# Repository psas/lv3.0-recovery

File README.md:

# lv3_recovery
Recovery system design and analysis.

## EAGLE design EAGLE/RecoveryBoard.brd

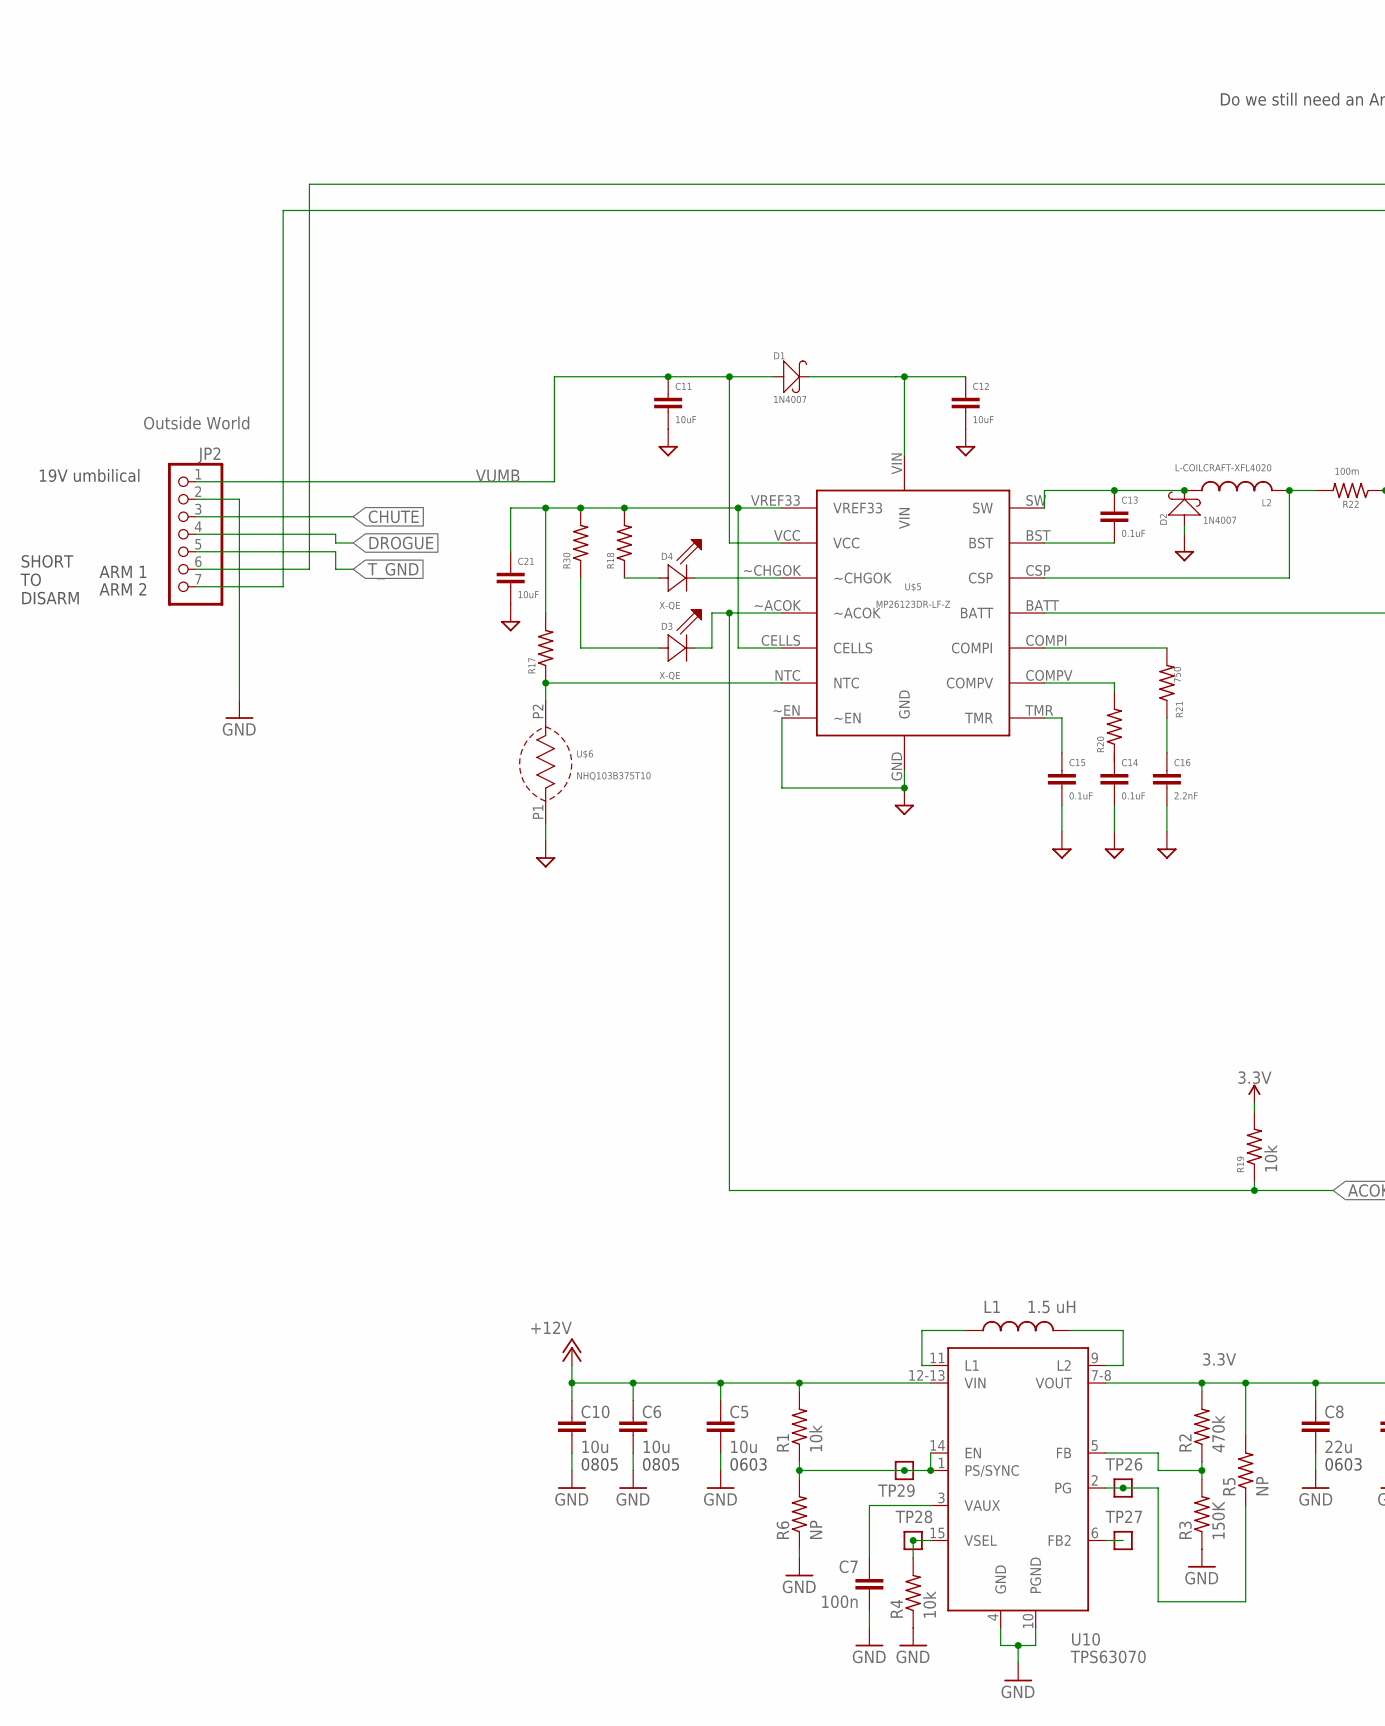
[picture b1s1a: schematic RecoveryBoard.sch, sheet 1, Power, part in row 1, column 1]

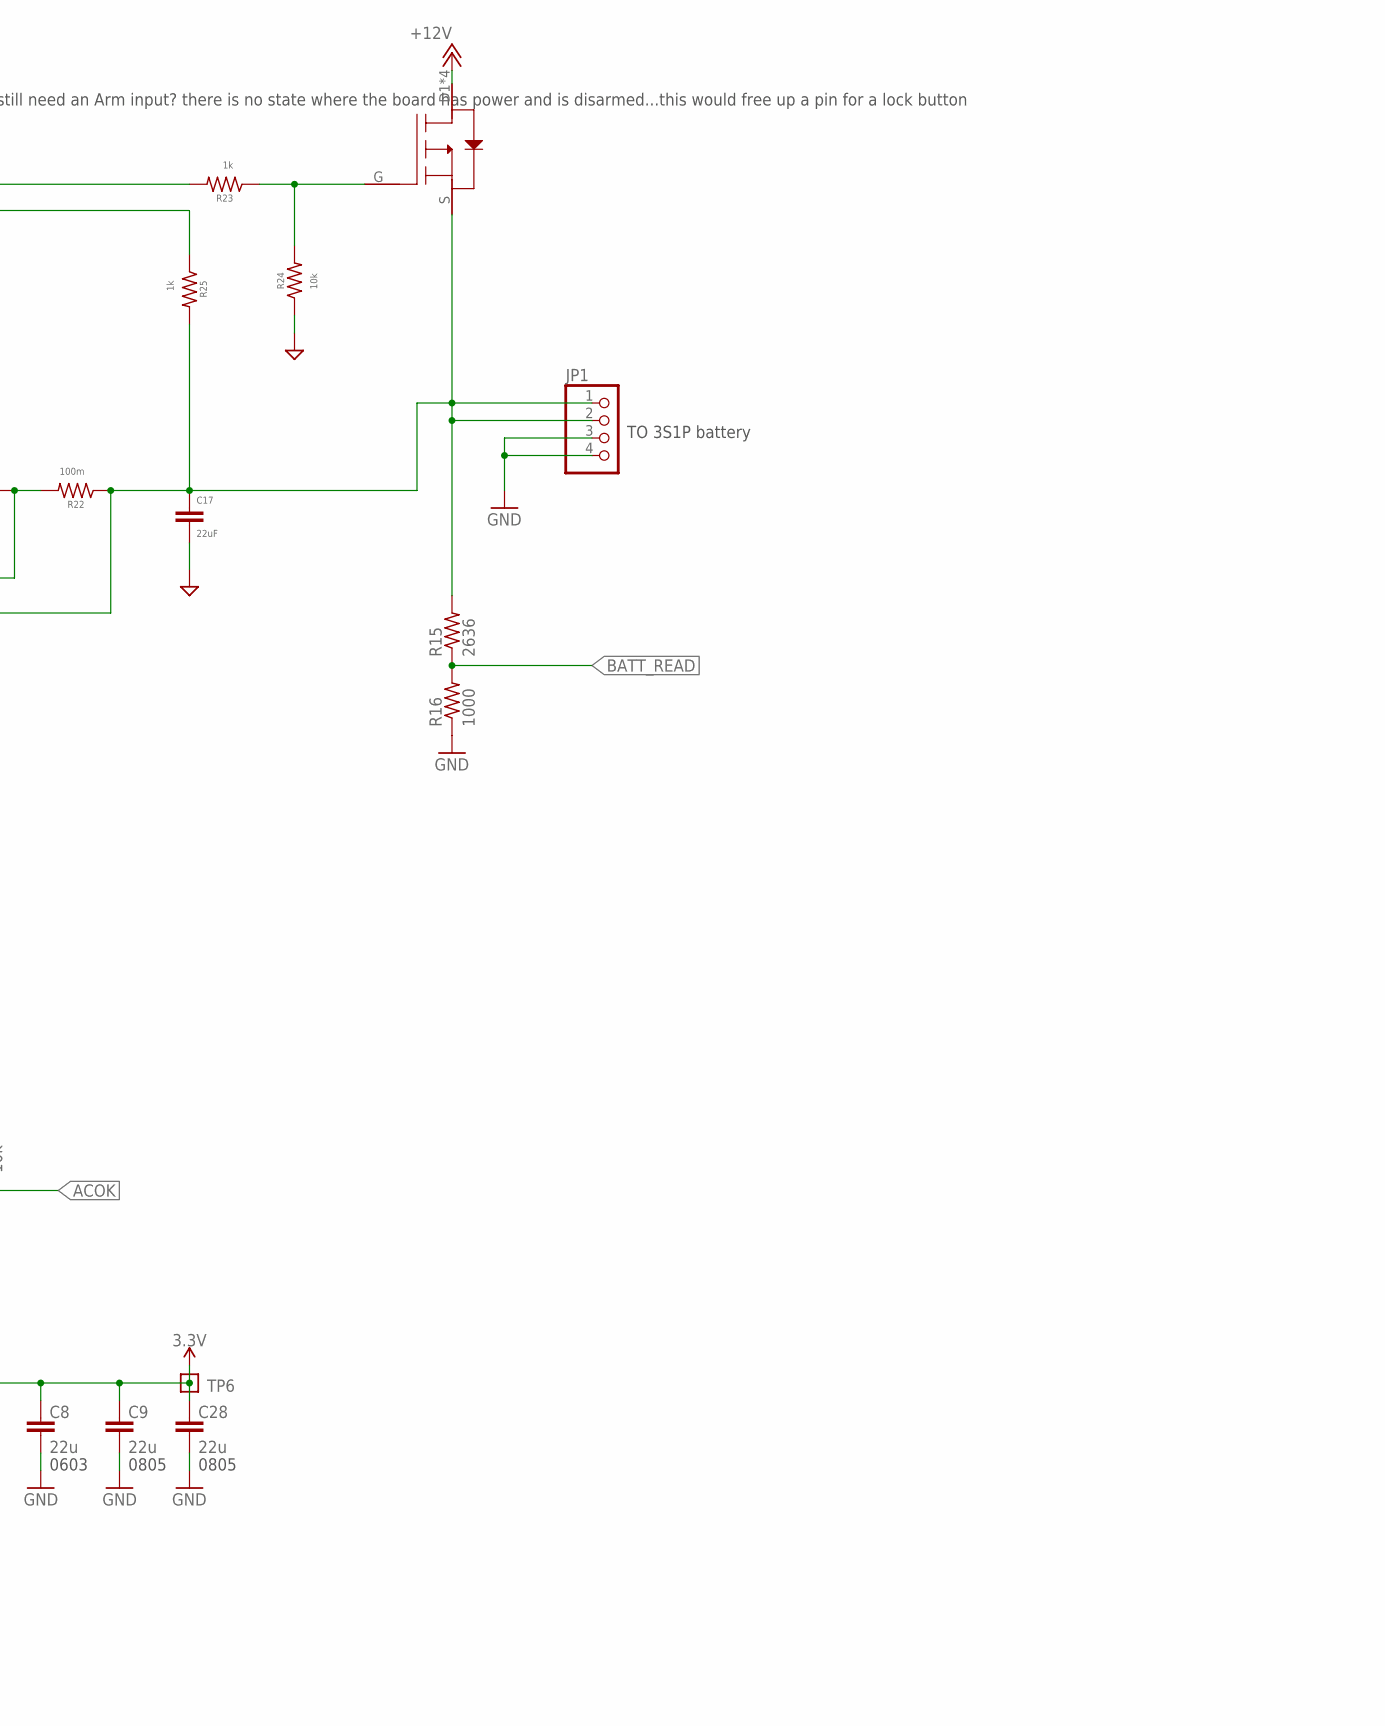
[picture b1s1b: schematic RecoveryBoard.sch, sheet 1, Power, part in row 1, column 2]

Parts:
C5: 10u; .0603-B-NOSILK; MPN CL05B104KO5NNNC
C6, C10: 10u; .0805-B-NOSILK
C7: 100n; .0402-B-NOSILK; MPN CL05B104KO5NNNC
C8: 22u; .0603-B-NOSILK; MPN CL05B104KO5NNNC
C9, C28: 22u; .0805-B-NOSILK
C11, C12, C21: 10uF; .0805-C-NOSILK
C13, C14, C15: 0.1uF; .0603-C-NOSILK
C16: 2.2nF; .0603-C-NOSILK
C17: 22uF; .0603-C-NOSILK
D1, D2: 1N4007; DO-214AC
D3, D4: X-QE
JP1: PINHD-1X4; 1X04
JP2: PINHD-1X7; 1X07
L1: 1.5 uH; L-COILCRAFT-XFL4020; MPN XFL4020-152ME
L2: L-COILCRAFT-XFL4020
R1, R4: 10k; .0402-B-NOSILK; MPN RC1005F6653CS
R2: 470k; .0402-B-NOSILK; MPN RC1005F6653CS
R3: 150K; .0402-B-NOSILK; MPN RC1005F6653CS
R5, R6: NP; .0402-B-NOSILK; MPN RC1005F6653CS
R15: 2636; .0603-C-NOSILK; MPN RC1005F6653CS
R16: 1000; .0603-C-NOSILK; MPN RC1005F6653CS
R17, R18, R20, R30: R-US_0603-C-NOSILK; .0603-C-NOSILK
R19, R24: 10k; .0603-C-NOSILK
R21: 750; .0603-C-NOSILK
R22: 100m; 1206-C
R23, R25: 1k; .0603-C-NOSILK
TP6, TP26, TP27, TP28, TP29: TEST-POINT; 2MM-TEST-POINT
U10: TPS63070; TPS63070X
U$5: MP26123DR-LF-Z
U$6: NHQ103B375T10
U$8: AO6405

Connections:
3.3V: C8.1, C9.1, C28.1, R2.2, R5.2, R19.2, TP6.1, U10.7-8 (VOUT); also elsewhere on the board
+12V: C5.1, C6.1, C10.1, R1.2, U10.12-13 (VIN), U$8.D1 (D), U$8.D2 (D), U$8.D3 (D), U$8.D4 (D); also elsewhere on the board
ACOK: D3.CATHODE (C), R19.1, U$5.~ACOK; also elsewhere on the board
BATT_READ: R15.1, R16.2; also elsewhere on the board
CHUTE: JP2.3; also elsewhere on the board
DROGUE: JP2.4; also elsewhere on the board
GND: C5.2, C6.2, C7.2, C8.2, C9.2, C10.2, C11.2, C12.2, C14.2, C15.2, C16.2, C17.2, C21.2, C28.2, D2.1 (+), JP1.3, JP1.4, JP2.2, R3.1, R4.1, R6.1, R16.1, R24.1, U10.4 (GND), U10.10 (PGND), U$5.EP, U$5.GND, U$5.~EN, U$6.P1; also elsewhere on the board
unnamed: C12.1, D1.2 (-), U$5.VIN
unnamed: C13.1, D2.2 (-), L2.1, U$5.SW
unnamed: C13.2, U$5.BST
unnamed: C21.1, R17.2, R18.2, R30.2, U$5.CELLS, U$5.VREF33
unnamed: D4.CATHODE (C), U$5.~CHGOK
unnamed: D3.ANODE (A), R30.1
unnamed: JP2.6, R23.2
unnamed: R23.1, R24.2, U$8.G
unnamed: D4.ANODE (A), R18.1
unnamed: R20.2, U$5.COMPV
unnamed: C15.1, U$5.TMR
unnamed: R17.1, U$5.NTC, U$6.P2
unnamed: R21.2, U$5.COMPI
unnamed: C16.1, R21.1
unnamed: C17.1, JP1.1, JP1.2, R15.2, R22.1, R25.2, U$5.BATT, U$8.S
unnamed: L2.2, R22.2, U$5.CSP
unnamed: C14.1, R20.1
TPS-EN: R1.1, R6.2, TP29.1, U10.1 (PS/SYNC), U10.14 (EN)
TPS-FB: R2.1, R3.2, U10.5 (FB)
TPS-FB2: TP27.1, U10.6 (FB2)
TPS-L1: L1.1, U10.11 (L1)
TPS-L2: L1.2, U10.9 (L2)
TPS-PG: R5.1, TP26.1, U10.2 (PG)
TPS-VAUX: C7.1, U10.3 (VAUX)
TPS-VSEL: R4.2, TP28.1, U10.15 (VSEL)
T_GND: JP2.5; also elsewhere on the board
VBAT: JP2.7, R25.1
VUMB: C11.1, D1.1 (+), JP2.1, U$5.VCC

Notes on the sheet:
0603
0805
Outside World
TO 3S1P battery
ARM 1
ARM 2
SHORT TO DISARM
19V umbilical
Do we still need an Arm input? there is no state where the board has power and is disarmed...this would free up a pin for a lock button

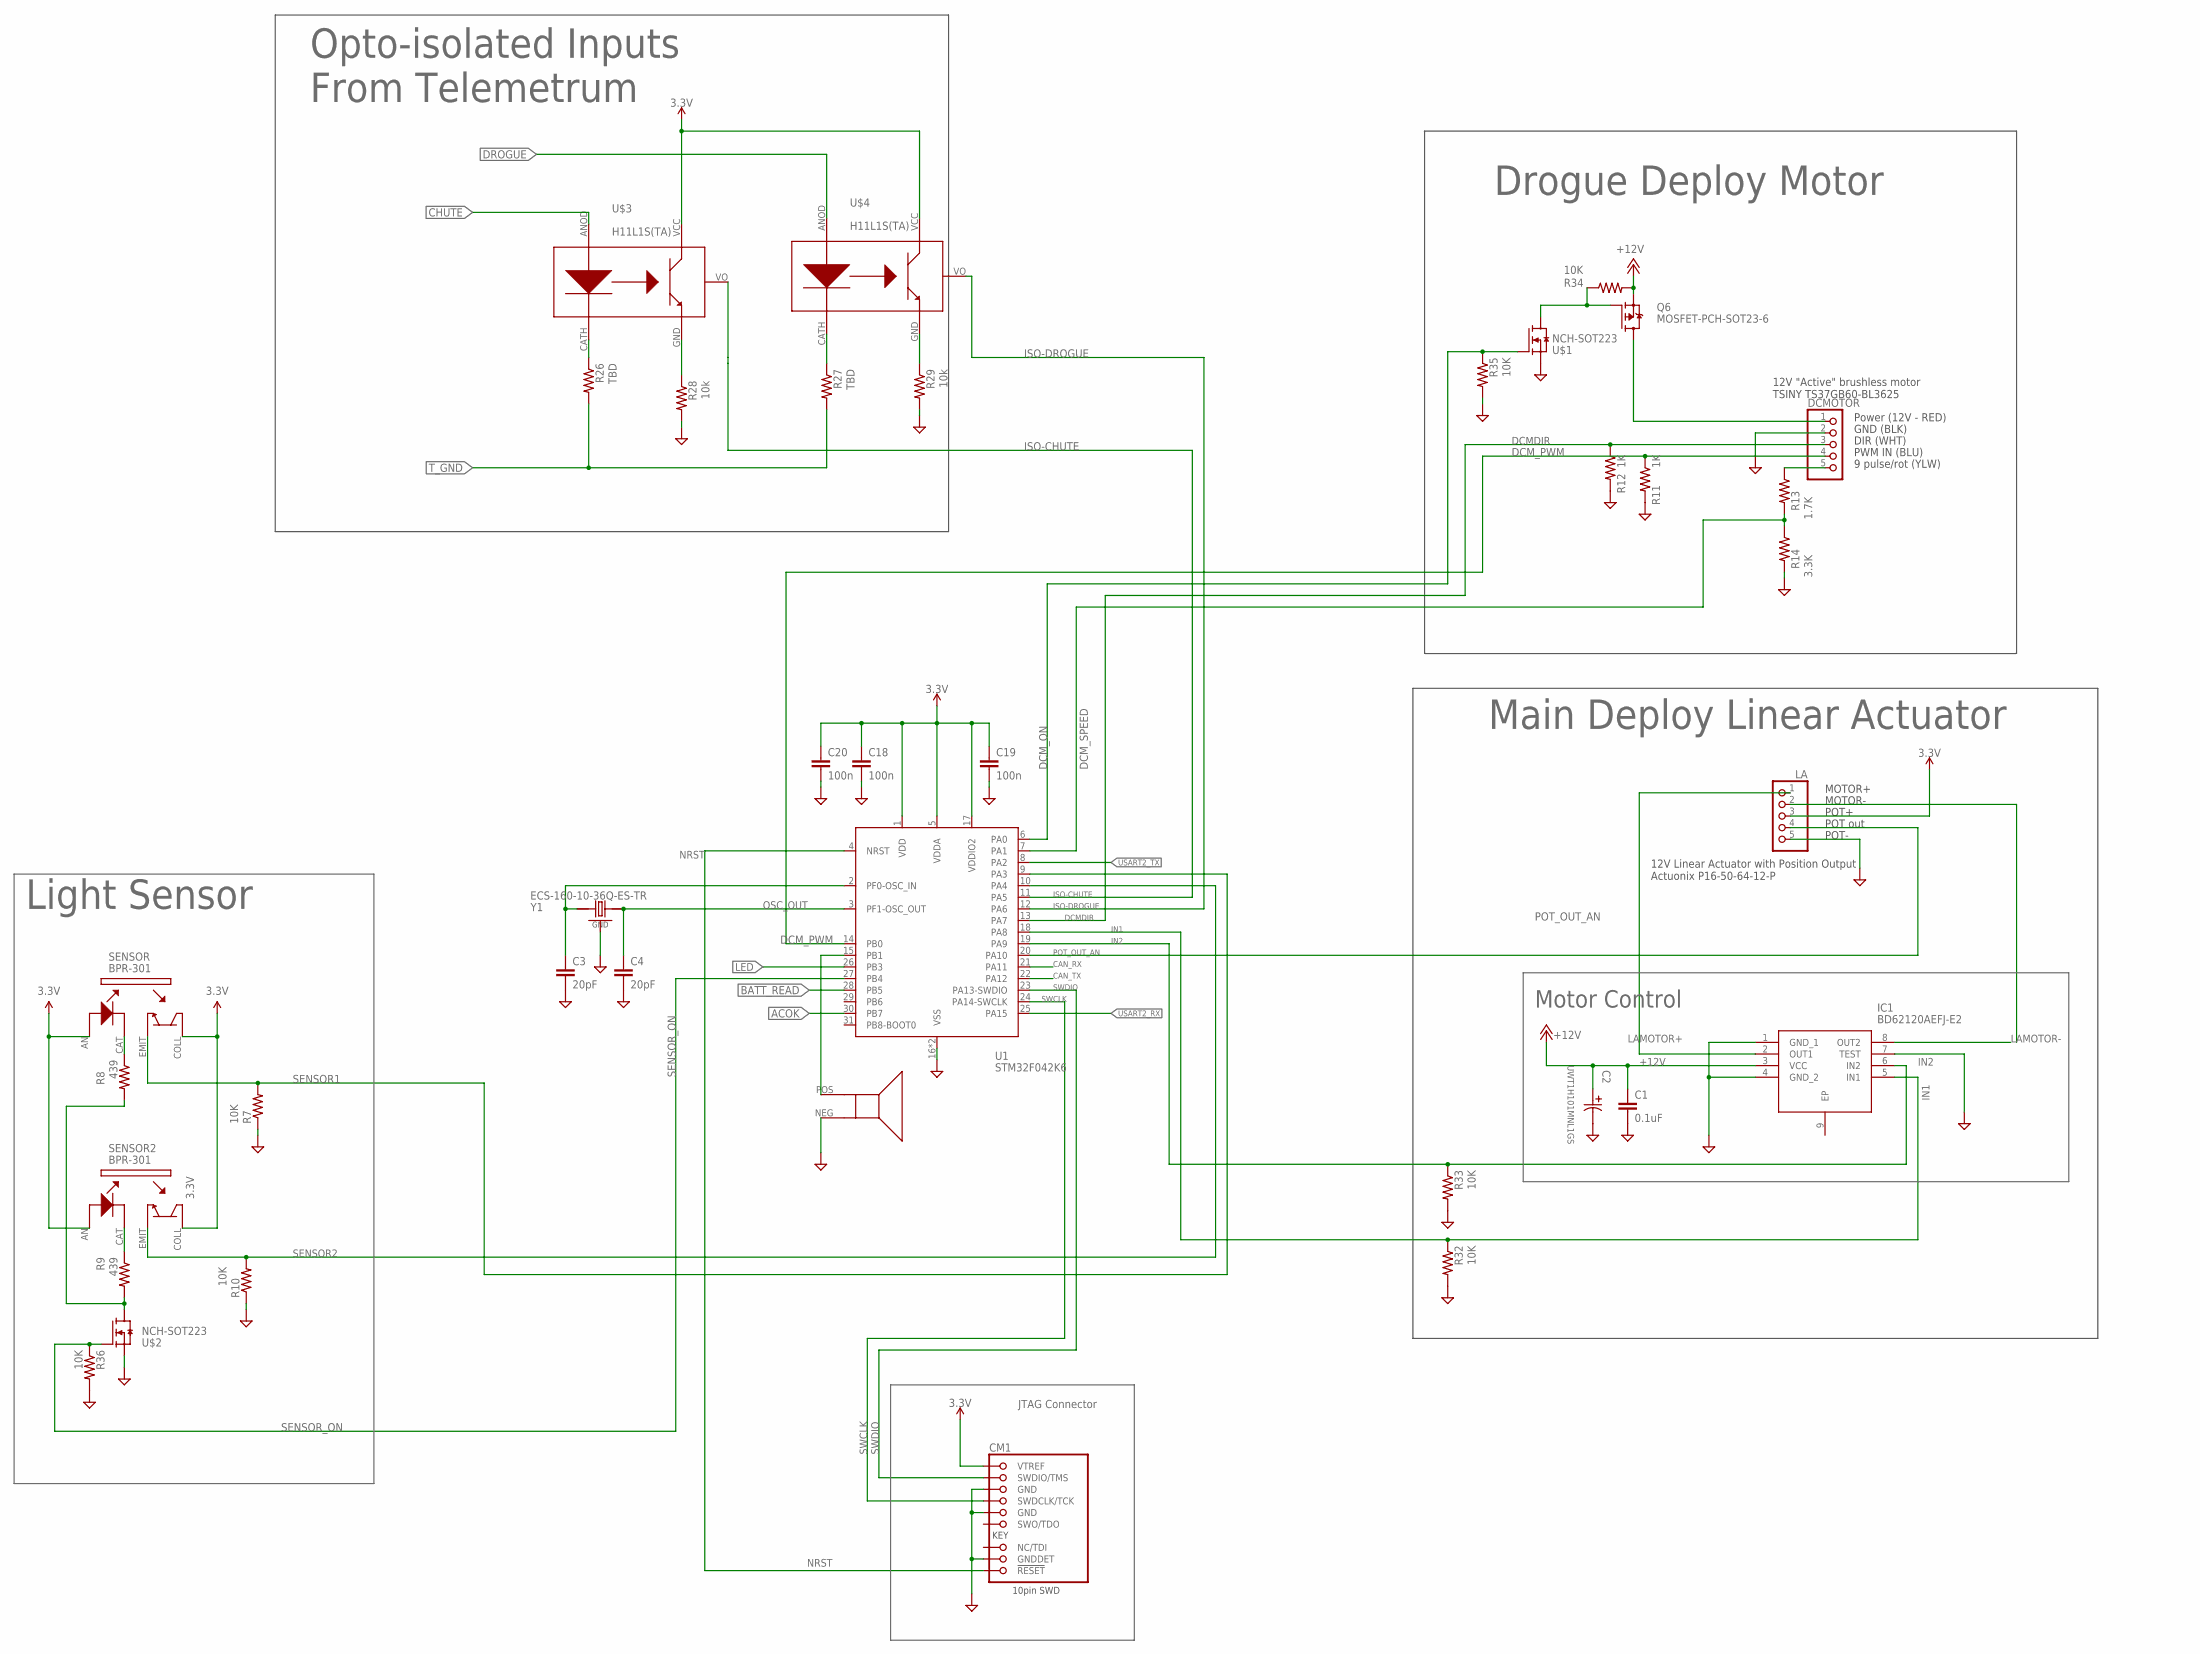
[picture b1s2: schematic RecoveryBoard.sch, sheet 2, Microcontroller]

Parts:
C1: 0.1uF; C0402
C2: UWT1H101MNL1GS; PCAP_8X10-ELECT
C3, C4: 20pF; C0402
C18, C19, C20: 100n; C0402
CM1: FTSH-105-XX-X-DV-K; CON10_2X5_DUK_FTSH
DCMOTOR: PINHD-1X5; 1X05
IC1: BD62120AEFJ-E2; SOIC127P600X100-9N
LA: PINHD-1X5; 1X05
Q6: MOSFET-PCH-SOT23-6; SOT23-6
R7, R10, R32, R33, R34, R35, R36: 10K; R0402
R8, R9: 439; R0402
R11, R12: 1K; R0402
R13: 1.7K; R0402
R14: 3.3K; R0402
R26, R27: TBD; R0402
R28, R29: 10k; R0402
SENSOR, SENSOR2: BPR-301
U1: STM32F042K6; QFP32-7X7
U$1, U$2: NCH-SOT223; SOT223
U$3, U$4: H11L1S(TA)
U$7: SMT-0440-S-R
Y1: ECS-160-10-36Q-ES-TR; XTAL_ECS-160-10-36Q-ES-TR

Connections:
3.3V: C18.1, C19.1, C20.1, CM1.1 (VTREF), LA.3, SENSOR.AN (ANOD), SENSOR.COLL, SENSOR2.AN (ANOD), SENSOR2.COLL, U1.1 (VDD), U1.5 (VDDA), U1.17 (VDDIO2), U$3.VCC (COLL), U$4.VCC (COLL); also elsewhere on the board
+12V: C1.1, C2.1, IC1.3 (VCC), Q6.4 (S), R34.2; also elsewhere on the board
ACOK: U1.30 (PB7); also elsewhere on the board
BATT_READ: U1.28 (PB5); also elsewhere on the board
CAN_RX: U1.21 (PA11)
CAN_TX: U1.22 (PA12)
CHUTE: U$3.ANOD; also elsewhere on the board
DCM+: DCMOTOR.1, Q6.1 (D), Q6.2 (D), Q6.5 (D), Q6.6 (D)
DCMDIR: DCMOTOR.3, R12.1, U1.13 (PA7)
DCM_ON: R35.1, U1.6 (PA0), U$1.1 (G)
DCM_PWM: DCMOTOR.4, R11.1, U1.14 (PB0)
DCM_SPEED: R13.2, R14.1, U1.7 (PA1)
DROGUE: U$4.ANOD; also elsewhere on the board
GND: C1.2, C2.2, C3.2, C4.2, C18.2, C19.2, C20.2, CM1.3 (GND), CM1.5 (GND), CM1.9 (GNDDET), DCMOTOR.2, IC1.1 (GND_1), IC1.4 (GND_2), IC1.7 (TEST), LA.5, R7.1, R10.1, R11.2, R12.2, R14.2, R28.2, R29.2, R32.2, R33.2, R35.2, R36.2, U1.16 (VSS), U1.32 (VSS), U$1.3 (S), U$2.3 (S), U$7.NEG, Y1.GND, Y1.GND2 (GND); also elsewhere on the board
IN1: IC1.5 (IN1), R32.1, U1.18 (PA8)
IN2: IC1.6 (IN2), R33.1, U1.19 (PA9)
ISO-CHUTE: U1.11 (PA5), U$3.VO (OUTPUT)
ISO-DROGUE: U1.12 (PA6), U$4.VO (OUTPUT)
LAMOTOR+: IC1.2 (OUT1), LA.1
LED: U1.26 (PB3)
unnamed: R8.1, SENSOR.CAT (CATH)
unnamed: C3.1, U1.2 (PF0-OSC_IN), Y1.IN/OUT
unnamed: R9.1, SENSOR2.CAT (CATH)
unnamed: Q6.3 (G), R34.1, U$1.2 (D), U$1.4 (D)
unnamed: R26.1, U$3.CATH (CAT)
unnamed: U1.15 (PB1), U$7.POS
unnamed: R28.1, U$3.GND (EMIT)
unnamed: R27.1, U$4.CATH (CAT)
unnamed: R8.2, R9.2, U$2.2 (D), U$2.4 (D)
unnamed: R29.1, U$4.GND (EMIT)
NRST: CM1.10 (!RESET), U1.4 (NRST)
OSC_OUT: C4.1, U1.3 (PF1-OSC_OUT), Y1.OUT/IN
POT_OUT_AN: LA.4, U1.20 (PA10)
PULSEOUT: DCMOTOR.5, R13.1
SENSOR1: R7.2, SENSOR.EMIT, U1.9 (PA3)
SENSOR2: R10.2, SENSOR2.EMIT, U1.10 (PA4)
SENSOR_ON: R36.1, U1.27 (PB4), U$2.1 (G)
SWCLK: CM1.4 (SWDCLK/TCK), U1.24 (PA14-SWCLK)
SWDIO: CM1.2 (SWDIO/TMS), U1.23 (PA13-SWDIO)
T_GND: R26.2, R27.2; also elsewhere on the board
USART2_RX: U1.25 (PA15)
USART2_TX: U1.8 (PA2)

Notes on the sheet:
Motor Control
Light Sensor
JTAG Connector
12V Linear Actuator with Position Output Actuonix P16-50-64-12-P
12V "Active" brushless motor TSINY TS37GB60-BL3625
MOTOR+
MOTOR-
POT+
POT out
POT-
Power (12V - RED)
GND (BLK)
DIR (WHT)
PWM IN (BLU)
9 pulse/rot (YLW)
Opto-isolated Inputs From Telemetrum
Drogue Deploy Motor
Main Deploy Linear Actuator

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
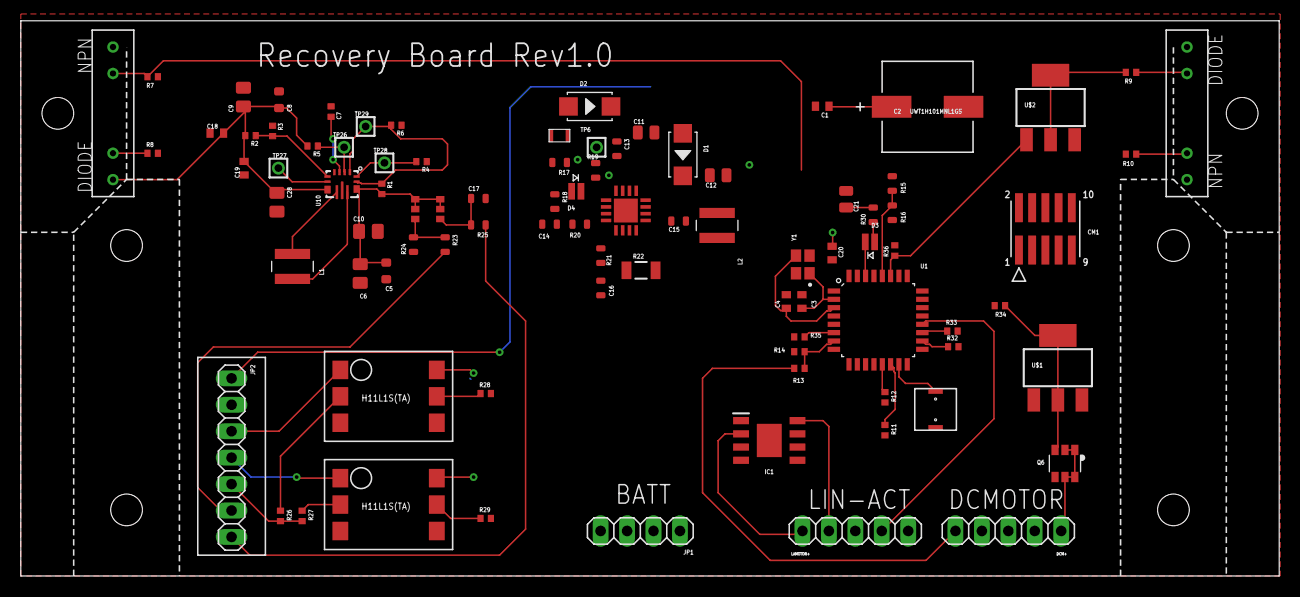
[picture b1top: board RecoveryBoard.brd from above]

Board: 2 copper layers, 120.9 x 53.3 mm, 88 parts (0 on the bottom side), 65 nets.

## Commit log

2016-07-29 First additions to the repo
2016-07-31 Having troubles with telemetry data. Need to find LV2 terminal velocity.
2016-08-03 Found impulse, worked on area estimation. Need to decide on style of parachute. Why did we choose x-form for LV2?
2016-08-04 added suggestions for using acceleration data
2016-08-10 Cleaning up formating and non-useful information
2016-08-16 Added parachute information
2016-08-16 best guess at the available nose cone volume
    It's 485 cubic inches.
    The notebook also includes a plot depicting that space.
2016-08-17 Added volume estimate
2016-08-24 Organizing, adding pics..why are a couple of pics automatically rotated?????? >:(
2016-09-06 Adding SW drawing of attachment ring
2016-09-06 Added Spring Ring CAD and Drawing
2016-09-06 Updated ring; removed v-band notch per Jorden
2016-09-07 The SW files are actually in here this time..
2016-10-17 Added tech drawing for ring r5; Still needed: tubing hole dimensioning, selection of tolerances, slip fit definition
2016-10-18 Added prelim drawing of spring ring r5
2016-11-07 Yay made the spring ring simpler and easier and more reliable
2017-01-10 Start of overview notebook. Cropped some photos
2017-01-10 worked on overview notebook
2017-01-23 Code structure in C
2017-01-29 adjusted int to uintx_t
2017-01-29 main line finished, error feedback set up, fail-safe created
2017-02-15 converted overview notebook to markdown file to show marie example of resizing images with markdown
2017-02-15 fixed file path for images
2017-02-15 converted markdown file to pdf to show example of resized images with the markdown syntax in the overview markdown file
2017-02-15 Worked on notebook
2017-06-16 Worked on design overview diagram
2017-06-17 Started line cutter model in SW
2017-08-28 Chute Test Videos
2017-08-31 Calculations for recovery drop test
2017-09-01 More drop test calcs_ignore final results for now
2017-09-01 double-checked calculations up to when the drogue goes taught
2017-09-02 more drop calcs
2017-09-02 numerical analysis of drogue (step e)
2017-09-02 changed formatting of the notebook to be all foldy
2017-09-02 moved input parameters to the start of the notebook
2017-09-02 prettied up the equations for the drogue stuff
2017-09-02 tried numerically solving the main chute stuff
    Aaaaaand it's totally irrelevant, since the main chute reaches steady
    state in under a second.
2017-09-02 made a nice chart of the system's trajectory
    Assuming there are no cross winds, you can input the wind velocity at
    the start, run the notebook, and get a chart of the trajectory (relative
    to the drop point) at the bottom of the notebook.
2017-09-02 added cross-wind and compass coordinate stuff
    Input the aircraft and wind bearing at the top of the notebook. Restart
    the kernel and run all cells. look a the charts at the end of the
    notebook. That will tell you the predicted trajectory of the system.
2017-09-02 little bit of drop calc work
2017-09-02 drop test calcs edit
2017-09-02 drop calc updates
2017-09-02 undid some hard-coding in section e
    The speed of the plane in the symbolic expression was hard-coded as 50
    m/s. It is now referenced to the speed of the plane at the start of the
    script.
2017-09-02 fixed typo in drogue deployment step
    I got confused with what was supposed to be put into the symbolic
    equation in step e. That term on the end is suppsed to be the drogue
    line length (now stored in the variable dl), NOT the plane's speed (Ps),
    which I had written. Whoops.
2017-09-04 GUI interface for linux, bootloader to allow firmware uploads through GUI
2017-09-04 Add files via upload
    Linux GUI interface for VESC
2017-09-04 Allows you to update firmware from bldc GUI in linux
2017-09-04 Firmware for VESC +custom application
2017-09-22 Just making sure everything is up-to-date
2017-10-15 Updated with 8 mph and winds from the SE, and a 10 second pause for line cutters.
2017-10-15 started a mission patch for the eNSR
2017-10-15 added eNSR and line-cutter timing to flight plan
2018-01-09 not sure what's getting updated with this push..
2018-01-09 Pulled upstream drop test calc
2018-02-14 Added plate for the VESC motor controller. Originally lasercut out of acrylic, but then realized we wanted an FR4 board so that's what we did! Made on the A4 with Haneef's help.
2018-02-24 Adding eNSR Cap (CAD by John and Marie)
2018-02-24 Spring ring update from 2016... never pushed
2018-04-12 Added LV2C Line cutter documentation from old PSAS archive. Markdown probably broken, so somebody please go and clean it up.
2018-05-17 The king rat that has become the firmware file for the eNSR
2018-12-26 getting up-to-date
2018-12-27 Organizing in prep for Capstone 2018-19
2019-01-24 example
2019-01-25 test
2019-01-26 rocket recovery prototype
2019-02-17 Uploading CAD files and Surgical Tubing Pull Test
2019-02-17 Created Assembly for 2nd Concept, deleted files non needed
2019-02-17 Updated assembly with motor based on old eNSR
2019-02-18 started drogue release/main deployment folder
2019-02-18 added drogue release/main deployment folder
2019-02-19 adding chute cups
2019-02-22 updated nose cone seperation rings
2019-02-26 adding CAD files mainly for 3 ring release design
2019-02-27 changing place of nose cone files
2019-03-05 Added CFD simulations for screw profiles
2019-03-07 Added Gabe's latest CAD
2019-03-17 Worked on system architecture assembly for Base 11 report
2019-03-18 CFD for Camera Ring + Updated assembly
2019-03-19 Update ST ring
2019-04-02 Made changes to bottom ring and ST ring
2019-04-04 Mainly changes to the 3-ring CAD, little bit of change within the NCSR assembly
2019-04-04 added motor and base assymbly
2019-04-04 Made edits to 3 ring CAD
2019-04-04 Inserted motor mount brkt into current_ncsr assy
2019-04-04 Making sure any new CAD updates are pushed
2019-04-05 added drawings and part edits per machine shop request
2019-04-05 Modeled the BLDC motor, modified the motor mounting bracket and updated assemblies
2019-04-05 Changed bottom ring and ST ring to be two parts again. This MUST happen so that the parts may be machined!
2019-04-05 Made bottom ring and ST ring separate parts again. This is needed for machining.
2019-04-05 making sure all CAD is up-to-date
2019-04-06 File organizing
2019-04-07 File organizing and drawing finalizing
2019-04-11 making sure everything is up-to-date
2019-04-12 Added pizza table and files for testing DCR
2019-04-12 motor mount work for NCS and DCR
2019-04-14 motor mnt design, pizza table design, 3 ring design edits
2019-04-16 Added radii to nubs due to interference
2019-04-27 working on DCR
2019-04-28 Added mockup with fasteners + ST_CAP
2019-04-30 updates to 3 ring assembly
2019-05-02 Arduino code files added for parachute testing
2019-05-03 Added new datalogger code for ground testing
2019-05-03 Update to datalogger
2019-05-04 Added 2 files for ST_CAP
2019-05-11 Updated assembly with new layout
2019-05-16 New keeper ring layout for webbing passthrough
2019-05-19 added files, including chute data
2019-05-19 Changed ST CAP
2019-05-22 add new 3 ring assembly
2019-05-23 added assembly V3.2 CAD
2019-06-13 added final assembly V3.2
2019-08-06 added parachute cups v3.0 & PIZZA Table v4
2019-08-14 updated trajectory simulation and new monte carlo analysis with some sample data for the impatient ones
2019-08-14 added aggregate stats
2019-09-17 Updated twist coupling to tighten up system
2019-09-17 Added drawing to submit to WPP for new twist coupling
2019-09-18 Added pdf and step file fore machining
2019-10-02 still need to document code but this is almost presentable
2019-10-14 got plots to work right, slight visual bug still, but not debilitating
2019-11-09 added skirt to twist coupleing for machining and standoff legs for pizza table
2019-11-11 fixed drawing files, added step files, removed standoffs w/o mount
2019-11-19 Designed new motor housing, added revised spacer ring, organized parts to be machined and 3d printed
2019-11-19 Removed temp files
2019-12-06 Remade pizza table, modified motor mount, craeted circuit board mock up an drawing, modified new motor gear and drawing
2019-12-06 changed gear filename to MotorGear-rev2 and added .pdf of drawing
2019-12-07 updated linear actuator bracket, added STL files for Adam to print in ../cad/formachining/STLfiles
2019-12-18 adding EAGLE files for recovery board
2019-12-18 updating lipo charging model
2019-12-18 adding files for sensors
2019-12-18 wiring f0
2019-12-18 adding terminal block
2019-12-18 terminal 2
2019-12-18 added resistance for sensors
2019-12-18 gitignore eagle backup files
2019-12-18 updating files
2019-12-19 handing off to dandrew
2019-12-20 implementing David's suggestions
2020-01-08 Removed old schematics, and drastically simplified overall system. See design review notes from today.
2020-01-08 design review 1
2020-01-08 1-8-2020
2020-01-08 cleanup
2020-01-09 created LiPo Library
2020-01-09 new lib
2020-01-09 deleted autosaves
2020-01-09 updated .gitignore
2020-01-09 updated gitignore finally working
2020-01-09 updated board to include LiPo charger, and the changes discussed after first design review
2020-01-10 updating STM32F0 pins
2020-01-10 added buzzer
2020-01-13 Fixed some power issues with Ben.
2020-01-13 Microcontroller and sensor board cleanup; added more to the outside world.
2020-01-13 board creation
2020-01-13 adding board and second design review
2020-01-14 starting grouping board components for layout
2020-01-15 beginning routing
2020-01-15 edited circuit board dimensions to fit sensor leads
2020-01-15 removed temp files that were open in Solidworks at timne of last commit
2020-01-15 Some fixes and polish.
2020-01-15 OCD moving around to put things in the right places and right names.
2020-01-15 OCD on package sizes 0603 for normal caps and resistors; 0805 for large caps, and larger yet for larger caps.
2020-01-15 beginning routing and placement
2020-01-15 finished routing
2020-01-15 finished routing and added TODO list
2020-01-16 More destruction on Ben's nice board. Good job Ben for putting up with Andrew.
2020-01-16 adding 1/15/2020 design notes with Andrew
2020-01-16 edited board after design meeting on 1/15
2020-01-16 adding my hotkey script
2020-01-20 added firmware state diagram and firmware folder
2020-01-20 updated state diagram
2020-01-22 adding new hbridge schematic
2020-01-22 adding libraries to repo and notes from design review
2020-01-22 implementing design changes from 1/21/2020
2020-01-22 created BOM
2020-01-23 completed BOM except for a couple pin head connectors
2020-01-25 updated bom
2020-01-25 creating digikey cart, but without pin connectors and jtag
2020-01-25 finished bom without jtag and connectors
2020-01-25 DRC after BOM update
2020-01-26 found samtec connector for jtag; still need pin connectors

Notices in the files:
parts and their libraries:
SparkFun-PowerSymbols: Licensing: Creative Commons ShareAlike 4.0 International - https://creativecommons.org/licenses/by-sa/4.0
